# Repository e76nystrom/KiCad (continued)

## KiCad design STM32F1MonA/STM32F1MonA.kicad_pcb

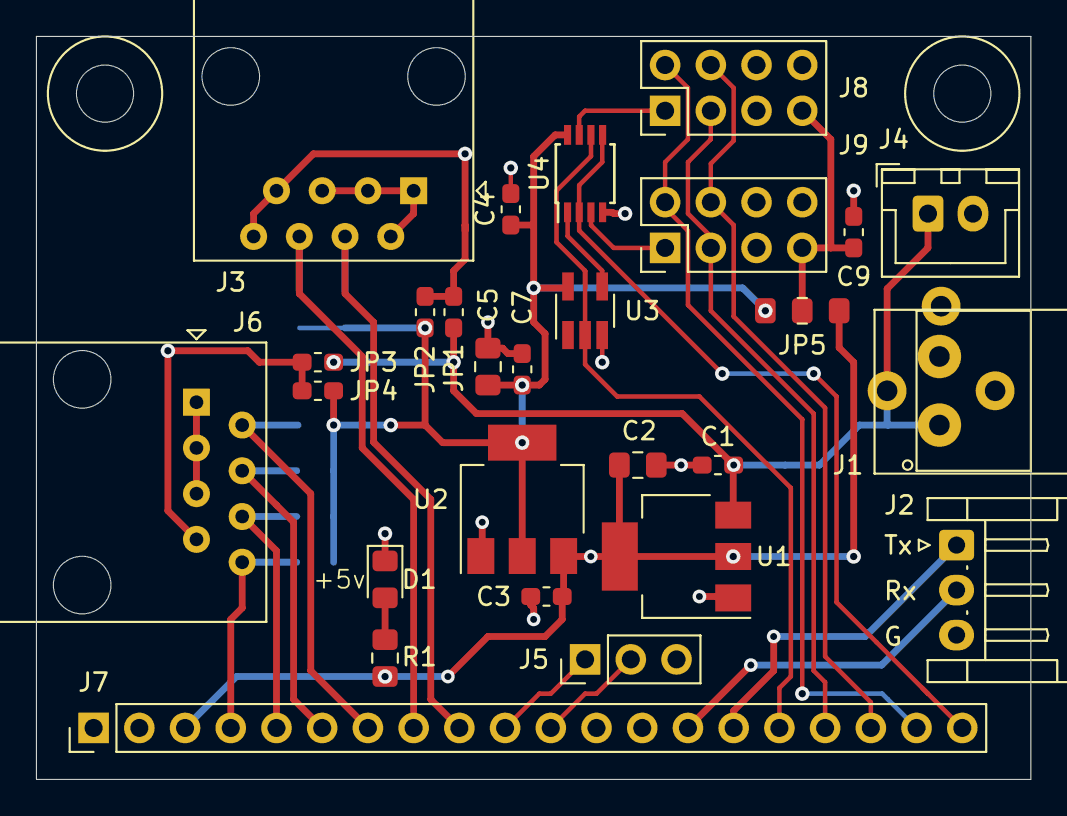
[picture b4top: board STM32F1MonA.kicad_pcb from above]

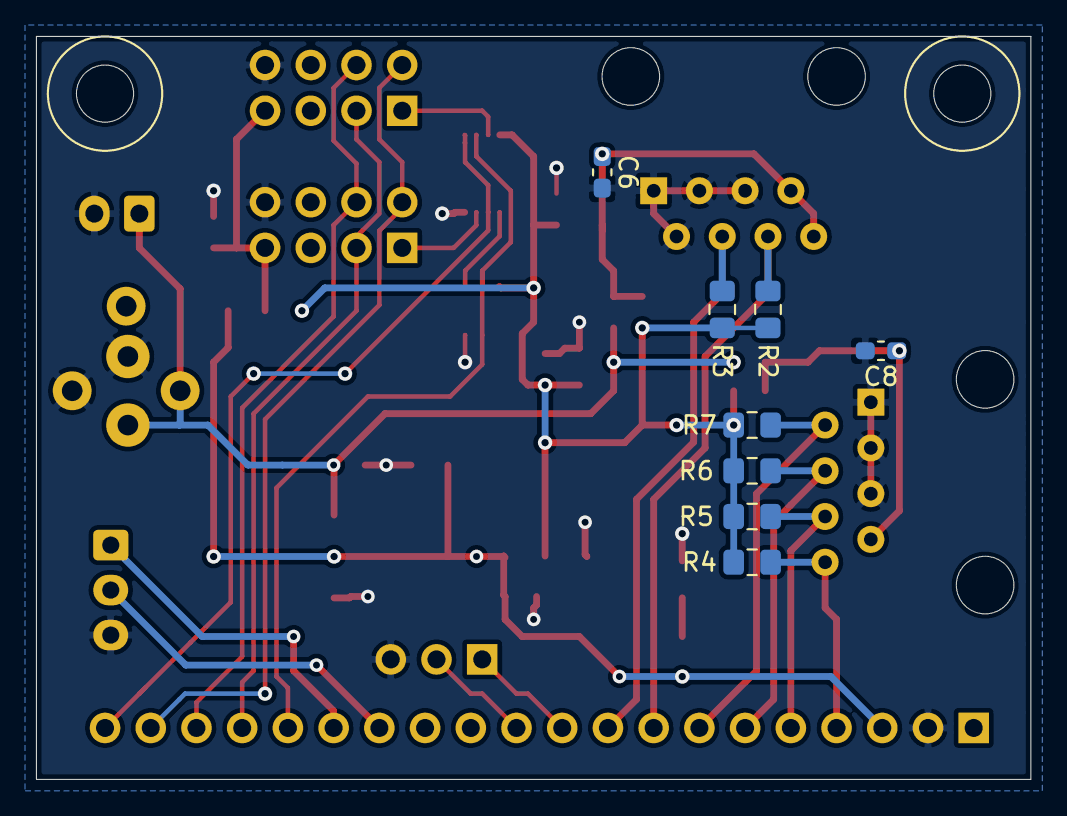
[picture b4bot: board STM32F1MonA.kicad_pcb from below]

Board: 2 copper layers, 55.2 x 41.3 mm, 37 parts (8 on the bottom side), 26 nets.

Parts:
C1, C3, C4, C6, C7, C8, C9: .1uf; C_0603_1608Metric_Pad1.05x0.95mm_HandSolder
C2, C5: 10u; C_0805_2012Metric_Pad1.15x1.40mm_HandSolder
D1: LED; D_0805_2012Metric_Pad1.15x1.40mm_HandSolder
H1, H2: MountingHole; MountingHole _1-8_1-4
J1: PJ-102; PJ-102-3.81mm
J2: Conn_01x03_Female; JST_EH_S3B-EH_1x03_P2.50mm_Horizontal
J3, J6: RJ45; RJ45_Amphenol_54602-x08_Horizontal
J4: Conn_01x02; JST_XH_B2B-XH-A_1x02_P2.50mm_Vertical
J5: Conn_01x03_Male; PinHeader_1x03_P2.54mm_Vertical
J7: Conn_01x20_Male; PinHeader_1x20_P2.54mm_Vertical
J8, J9: Conn_02x04_Odd_Even; PinHeader_2x04_P2.54mm_Vertical
JP1, JP2, JP3, JP4: Jumper_NO_Small; R_0603_1608Metric_Pad1.05x0.95mm_HandSolder
JP5: SolderJumper_3_Open; Jumper_0805_3
R1: 5.1k; R_0805_2012Metric_Pad1.15x1.40mm_HandSolder
R2, R3, R4, R5, R6, R7: R; R_0805_2012Metric_Pad1.15x1.40mm_HandSolder
U1: AP1117-50; SOT-223-3_TabPin2
U2: AP1117-33; SOT-223-3_TabPin2
U3: 74LVC1G04; SOT-23-5_HandSoldering
U4: 74LVC2G32; TSSOP-8_3x3mm_P0.65mm

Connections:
+3V3: C4.1, C5.1, C7.1, JP2.1, JP4.1, JP5.3, R2.1, R3.1, R4.1, R5.1, R6.1, R7.1, U2.2, U3.5, U4.8
+5V: C2.1, C3.1, J7.3, JP5.1, R1.1, U1.2, U2.3
/A8: J7.16, U3.2, U4.6
/A9: J2.1, J7.15
/A10: J2.2, J7.14
/A15: J5.2, J7.11
/B3: J5.1, J7.10
/B4: J3.4, J7.9, R3.2
/B5: J3.6, J7.8, R2.2
/B6: J6.2, J7.7, R7.2
/B7: J6.4, J7.6, R6.2
/B8: J6.6, J7.5, R5.2
/B9: J6.8, J7.4, R4.2
/B12: J7.20, U4.2, U4.5
/B13: J7.19, J8.2, J9.2
/B14: J7.18, J8.4, J9.4
/B15: J7.17, J8.3, J9.3
/LedR: D1.2, R1.2
/SensorPwr0: C6.1, J3.7, J3.8, JP1.2, JP2.2
/SensorPwr1: C8.1, J6.7, JP3.2, JP4.2
/VOut: C9.1, J8.7, J9.7, JP5.2
/Vin: C1.1, J1.1, J4.1, JP1.1, JP3.1, U1.3
/~CS0: J8.1, U4.7
/~CS1: J9.1, U4.3
/~Sel: U3.4, U4.1
GND: C1.2, C2.2, C3.2, C4.2, C5.2, C6.2, C7.2, C8.2, C9.2, D1.1, J1.2, J2.3, J3.1, J3.2, J3.3, J3.5, J4.2, J5.3, J6.1, J6.3, J6.5, J7.2, J8.8, J9.8, U1.1, U2.1, U3.3, U4.4

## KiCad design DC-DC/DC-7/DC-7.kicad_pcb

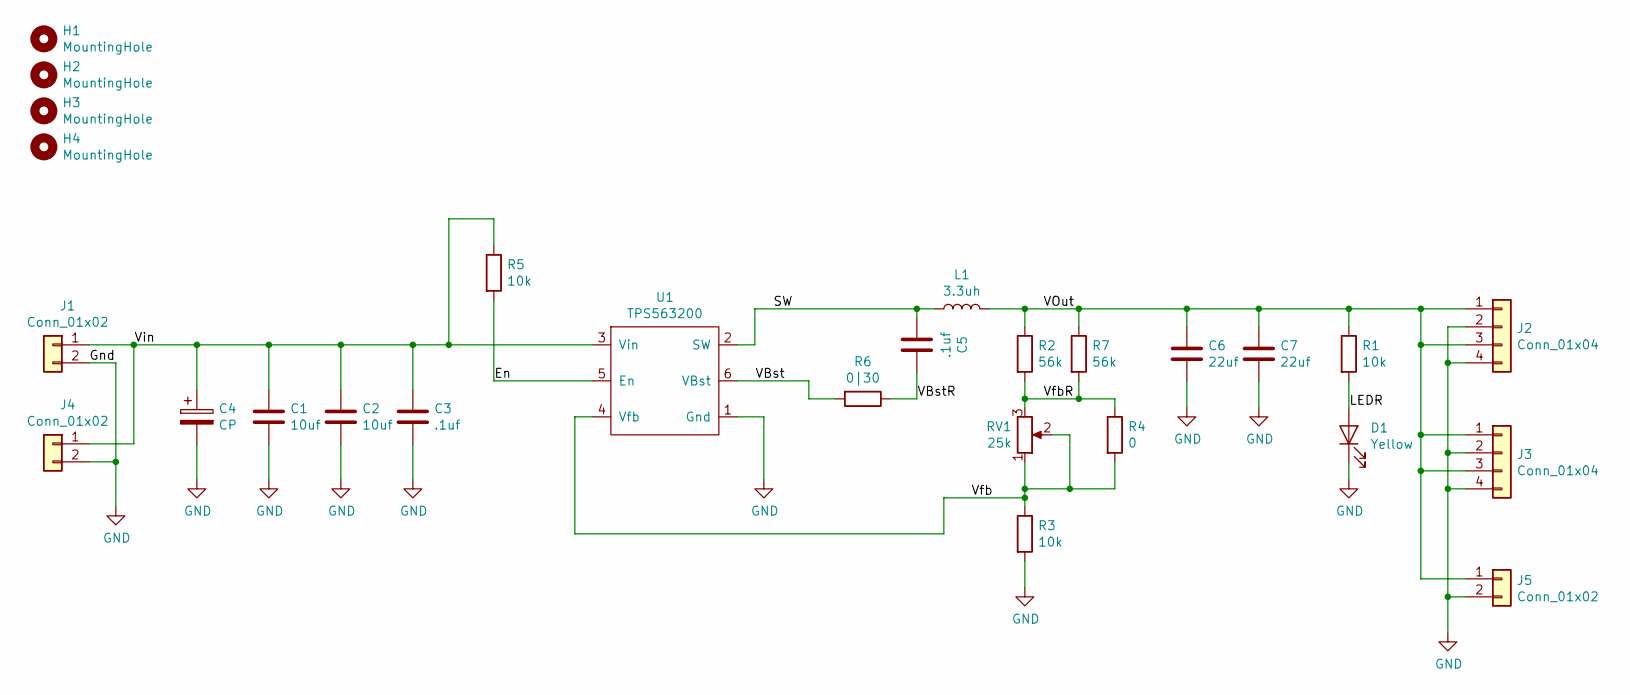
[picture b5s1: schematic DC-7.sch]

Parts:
C1, C2: 10uf; C_0603_1608Metric_Pad1.05x0.95mm_HandSolder
C3, C5: .1uf; C_0805_2012Metric_Pad1.15x1.40mm_HandSolder
C4: CP; CP_Radial_D10.0mm_P5.00mm
C6, C7: 22uf; C_1210_3225Metric_Pad1.42x2.65mm_HandSolder
D1: Yellow; LED_0805_2012Metric_Pad1.15x1.40mm_HandSolder
H1, H2, H3, H4: MountingHole; MountingHole _1-8_1-4
J1: Conn_01x02; 2 Pin 3.81mm
J2, J3: Conn_01x04; 4 Pin 3.81mm
J4, J5: Conn_01x02; PinHeader_1x02_P2.54mm_Vertical
L1: 3.3uh; KMP4800S
R1, R5: 10k; R_0805_2012Metric_Pad1.15x1.40mm_HandSolder
R2, R7: 56k; R_0805_2012Metric_Pad1.15x1.40mm_HandSolder
R3: 10k; R_0603_1608Metric_Pad1.05x0.95mm_HandSolder
R4: 0; R_0603_1608Metric_Pad1.05x0.95mm_HandSolder
R6: 0|30; R_0805_2012Metric_Pad1.15x1.40mm_HandSolder
RV1: 25k; Potentiometer_Bourns_3296W_Vertical
U1: TPS563200; SOT-23-6_Handsoldering

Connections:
/En: R5.2, U1.5 (En)
/LEDR: D1.2 (A), R1.2
/SW: C5.2, L1.1, U1.2 (SW)
/VBst: R6.2, U1.6 (VBst)
/VBstR: C5.1, R6.1
/VOut: C6.1, C7.1, J2.1, J2.3, J3.1, J3.3, J5.1, L1.2, R1.1, R2.1, R7.1
/Vfb: R3.1, R4.2, RV1.1, RV1.2, U1.4 (Vfb)
/VfbR: R2.2, R4.1, R7.2, RV1.3
/Vin: C1.1, C2.1, C3.1, C4.1, J1.1, J4.1, R5.1, U1.3 (Vin)
GND: C1.2, C2.2, C3.2, C4.2, C6.2, C7.2, D1.1 (K), J1.2, J2.2, J2.4, J3.2, J3.4, J4.2, J5.2, R3.2, U1.1 (Gnd)

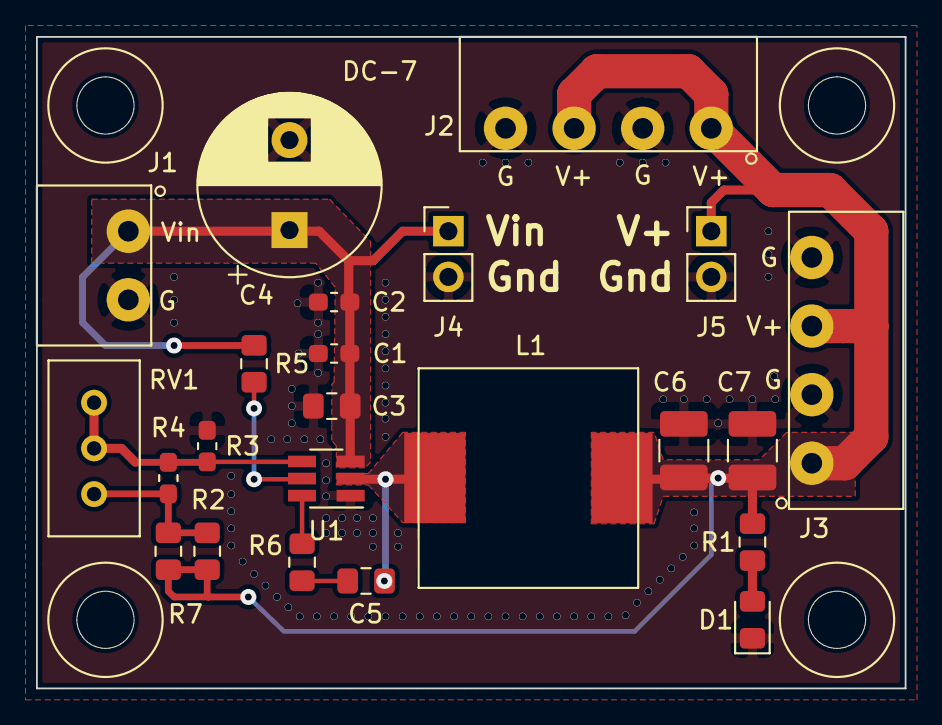
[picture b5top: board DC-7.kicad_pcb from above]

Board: 2 copper layers, 48.3 x 36.2 mm, 27 parts (0 on the bottom side), 10 nets.

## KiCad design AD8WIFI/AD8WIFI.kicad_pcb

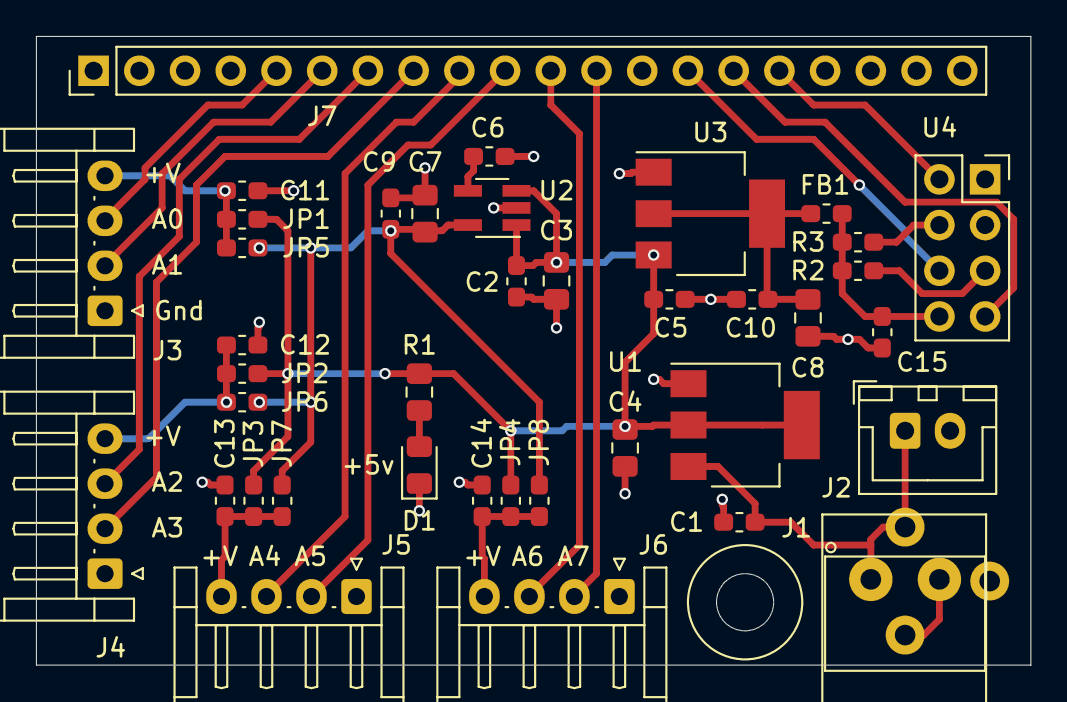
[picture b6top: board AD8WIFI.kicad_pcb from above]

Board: 2 copper layers, 55.2 x 34.9 mm, 40 parts (0 on the bottom side), 25 nets.

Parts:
C1, C2, C5, C9, C10, C11, C12, C13, C14, C15: .1uf; C_0603_1608Metric_Pad1.05x0.95mm_HandSolder
C3, C4, C7, C8: 10u; C_0805_2012Metric_Pad1.15x1.40mm_HandSolder
C6: .1u; C_0603_1608Metric_Pad1.05x0.95mm_HandSolder
D1: LED; D_0805_2012Metric_Pad1.15x1.40mm_HandSolder
FB1: Ferrite_Bead; L_0603_1608Metric_Pad1.05x0.95mm_HandSolder
H1: MountingHole; MountingHole _1-8_1-4
J1: PJ-102; PJ-102-3.81mm
J2: Conn_01x02; JST_XH_B2B-XH-A_1x02_P2.50mm_Vertical
J3, J4, J5, J6: Conn_01x04_Female; JST_EH_S4B-EH_1x04_P2.50mm_Horizontal
J7: Conn_01x20_Male; PinHeader_1x20_P2.54mm_Vertical
JP1, JP2, JP3, JP4, JP5, JP6, JP7, JP8: Jumper_NO_Small; R_0603_1608Metric_Pad1.05x0.95mm_HandSolder
R1: 5.1k; R_0805_2012Metric_Pad1.15x1.40mm_HandSolder
R2, R3: 10k; R_0603_1608Metric_Pad1.05x0.95mm_HandSolder
U1: AP1117-50; SOT-223-3_TabPin2
U2: RT9193; SOT-23-5_HandSoldering
U3: AP1117-33; SOT-223-3_TabPin2
U4: ESP8266; ESP-01

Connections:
+3V3: C7.1, C9.1, JP5.1, JP6.1, JP7.1, JP8.1, U2.5
+5V: C2.1, C3.1, C4.1, C5.1, JP1.1, JP2.1, JP3.1, JP4.1, R1.1, U1.2, U2.1, U2.3, U3.3
/3.3W: C8.1, C10.1, FB1.1, U3.2
/A0: J3.3, J7.5
/A1: J3.2, J7.6
/A2: J4.3, J7.7
/A3: J4.2, J7.8
/A4: J5.3, J7.9
/A5: J5.2, J7.10
/A6: J6.3, J7.11
/A7: J6.2, J7.12
/B1-Rst: J7.14, U4.6
/B10-Tx: J7.15, U4.7
/B11-Rx: J7.16, U4.2
/BP: C6.1, U2.4
/ESP3.3: C15.1, FB1.2, R2.1, R3.1, U4.8
/LedR: D1.2, R1.2
/Pu0: R2.2, U4.5
/Pu1: R3.2, U4.4
/VA0: C11.2, J3.4, JP1.2, JP5.2
/VA1: C12.2, J4.4, JP2.2, JP6.2
/VA2: C13.2, J5.4, JP3.2, JP7.2
/VA3: C14.2, J6.4, JP4.2, JP8.2
/Vin: C1.1, J1.1, J2.1, U1.3
GND: C1.2, C2.2, C3.2, C4.2, C5.2, C6.2, C7.2, C8.2, C9.2, C10.2, C11.1, C12.1, C13.1, C14.1, C15.2, D1.1, J1.2, J2.2, J3.1, J4.1, J5.1, J6.1, J7.19, J7.20, U1.1, U2.2, U3.1, U4.1

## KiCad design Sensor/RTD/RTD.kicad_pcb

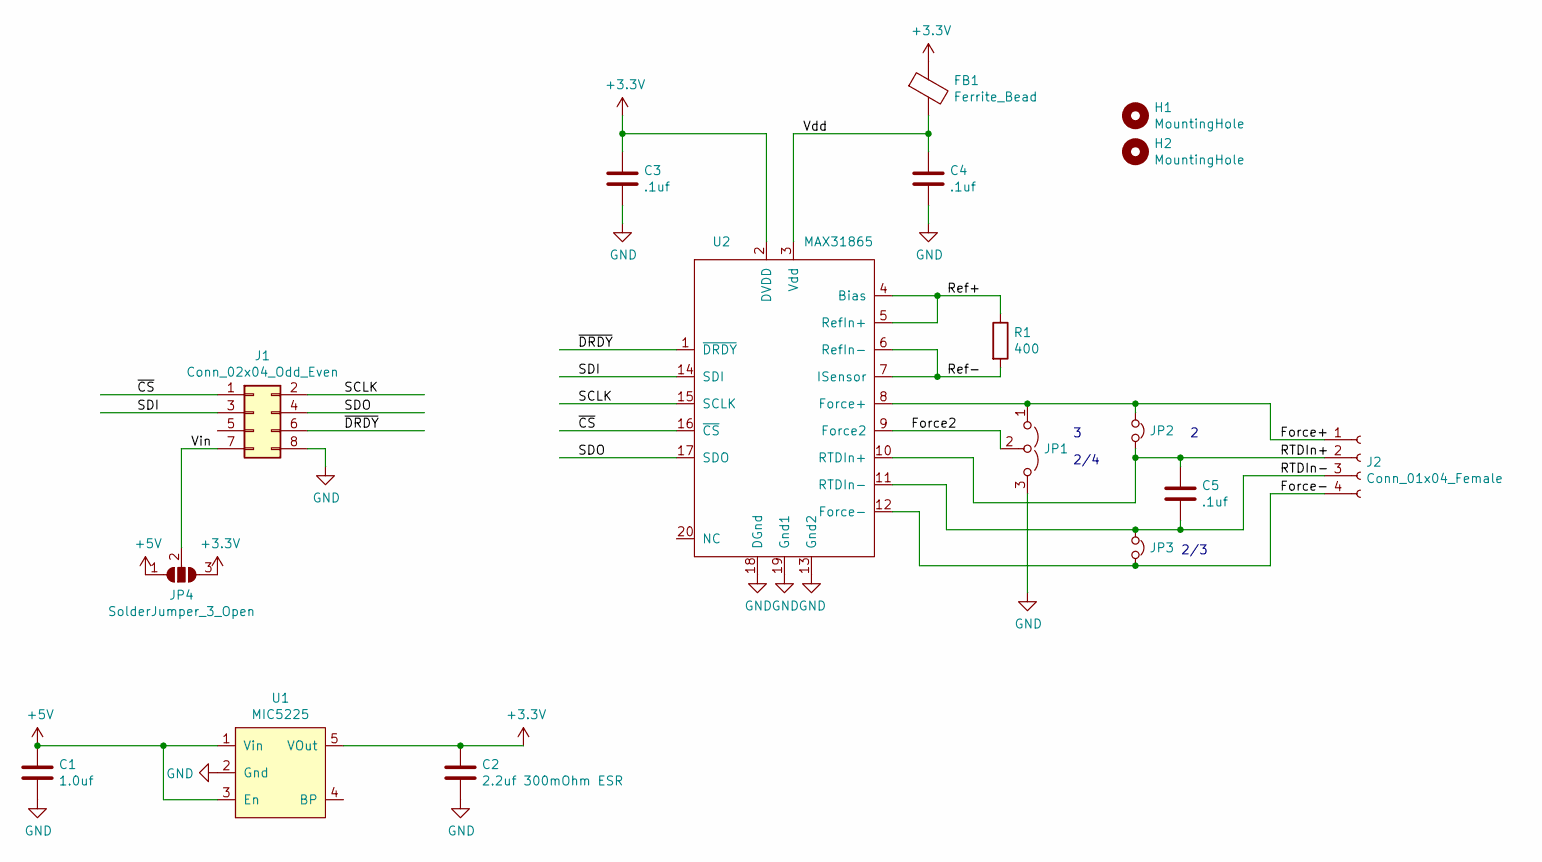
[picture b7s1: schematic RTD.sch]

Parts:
C1: 1.0uf; C_0805_2012Metric_Pad1.15x1.40mm_HandSolder
C2: 2.2uf 300mOhm ESR; C_0805_2012Metric_Pad1.15x1.40mm_HandSolder
C3, C4, C5: .1uf; C_0805_2012Metric_Pad1.15x1.40mm_HandSolder
FB1: Ferrite_Bead; L_0805_2012Metric_Pad1.15x1.40mm_HandSolder
H1, H2: MountingHole; MountingHole _1-8_1-4
J1: Conn_02x04_Odd_Even; PinHeader_2x04_P2.54mm_Vertical
J2: Conn_01x04_Female; PhoenixContact_MC_1,5_4-G-3.81_1x04_P3.81mm_Horizontal
JP1: SolderJumper-3_P1.3mm_Open_RoundedPad1.0x1.5mm_NumberLabels
JP2, JP3: SolderJumper-2_P1.3mm_Open_TrianglePad1.0x1.5mm
JP4: SolderJumper_3_Open; Jumper_0805_3
R1: 400; R_0805_2012Metric_Pad1.15x1.40mm_HandSolder
U1: MIC5225; SOT-23-5_HandSoldering
U2: MAX31865; TSSOP-20_4.4x6.5mm_P0.65mm_MAX

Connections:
+3V3: C2.1, C3.1, FB1.1, JP4.3 (B), U1.5 (VOut), U2.2 (DVDD)
+5V: C1.1, JP4.1 (A), U1.1 (Vin), U1.3 (En)
/Force2: JP1.2 (C), U2.9 (Force2)
/Force+: J2.1, JP1.1 (A), JP2.1, U2.8 (Force+)
/Force-: J2.4, JP3.2, U2.12 (Force-)
/RTDIn+: C5.1, J2.2, JP2.2, U2.10 (RTDIn+)
/RTDIn-: C5.2, J2.3, JP3.1, U2.11 (RTDIn-)
/Ref+: R1.1, U2.4 (Bias), U2.5 (RefIn+)
/Ref-: R1.2, U2.6 (RefIn-), U2.7 (ISensor)
/SCLK: J1.2, U2.15 (SCLK)
/SDI: J1.3, U2.14 (SDI)
/SDO: J1.4, U2.17 (SDO)
/Vdd: C4.2, FB1.2, U2.3 (Vdd)
/Vin: J1.7, JP4.2 (C)
/~CS: J1.1, U2.16 (~CS)
/~DRDY: J1.6, U2.1 (~DRDY)
GND: C1.2, C2.2, C3.2, C4.1, J1.8, JP1.3 (B), U1.2 (Gnd), U2.13 (Gnd2), U2.18 (DGnd), U2.19 (Gnd1)

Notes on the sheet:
2/4
2/3

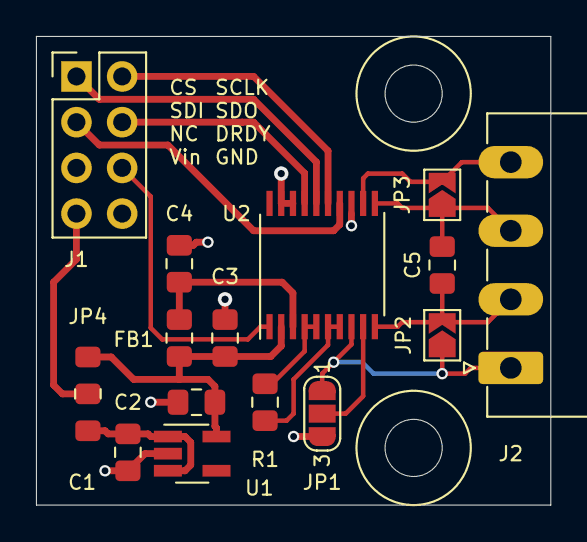
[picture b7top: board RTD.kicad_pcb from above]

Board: 2 copper layers, 28.6 x 26.0 mm, 17 parts (0 on the bottom side), 17 nets.

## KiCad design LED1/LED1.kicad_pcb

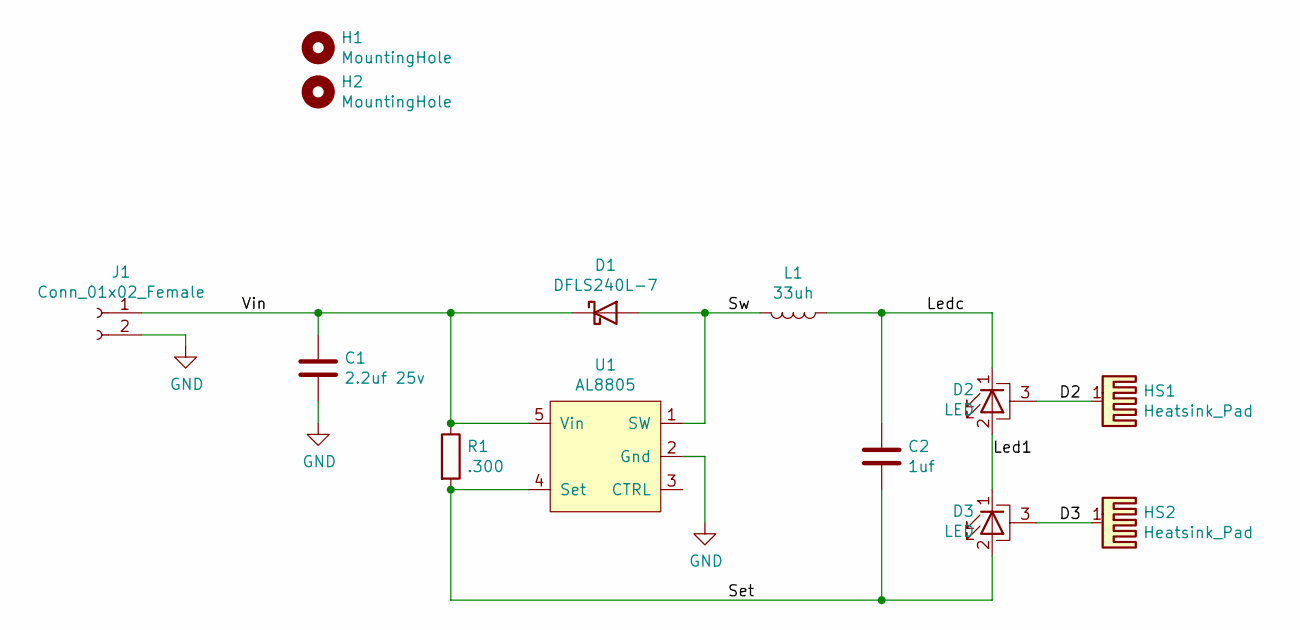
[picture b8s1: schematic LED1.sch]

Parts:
C1: 2.2uf 25v; C_0805_2012Metric_Pad1.15x1.40mm_HandSolder
C2: 1uf; C_1206_3216Metric_Pad1.42x1.75mm_HandSolder
D1: DFLS240L-7; D_SOD-123
D2, D3: LED; PowerLed
H1, H2: MountingHole; MountingHole _1-8_1-4
HS1, HS2: Heatsink_Pad
J1: Conn_01x02_Female; PhoenixContact_MC_1,5_2-G-3.81_1x02_P3.81mm_Horizontal
L1: 33uh; LPS-6235
R1: .300; R_0805_2012Metric_Pad1.15x1.40mm_HandSolder
U1: AL8805; SOT-23-5_HandSoldering

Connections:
/D2: D2.3 (PAD), HS1.1
/D3: D3.3 (PAD), HS2.1
/Led1: D2.2 (A), D3.1 (K)
/Ledc: C2.1, D2.1 (K), L1.1
/Set: C2.2, D3.2 (A), R1.2, U1.4 (Set)
/Sw: D1.2 (A), L1.2, U1.1 (SW)
/Vin: C1.1, D1.1 (K), J1.1, R1.1, U1.5 (Vin)
GND: C1.2, J1.2, U1.2 (Gnd)

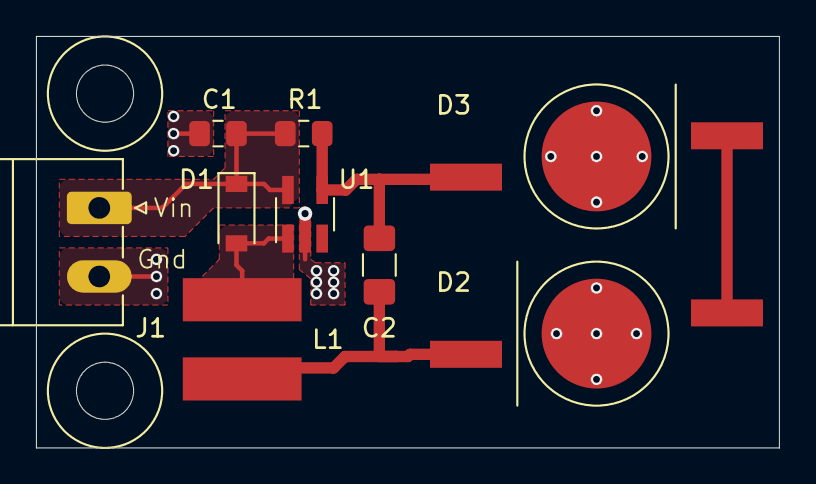
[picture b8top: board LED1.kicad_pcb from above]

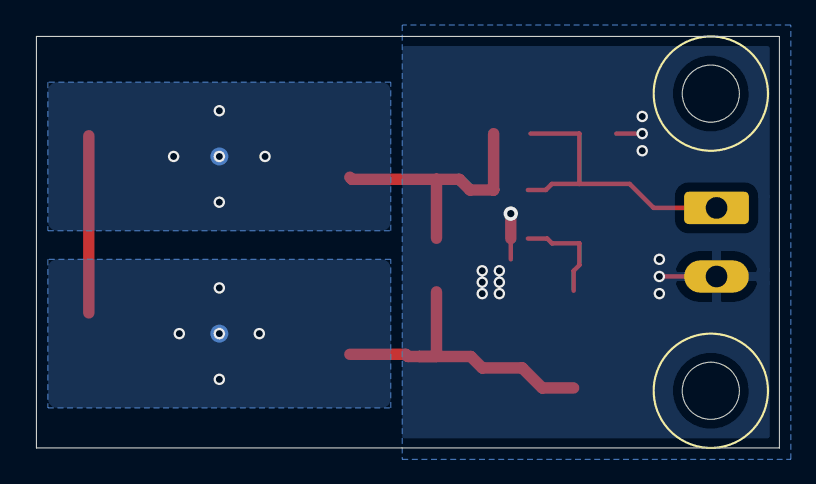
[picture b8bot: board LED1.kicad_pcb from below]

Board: 2 copper layers, 41.3 x 22.9 mm, 13 parts (2 on the bottom side), 8 nets.

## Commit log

2021-01-01 New layout for Mega Output. Part done
2021-01-01 Output Mega layout completed.
2021-01-01 Add labels to silk screen.
2021-01-03 Designed front panel. More updates to output.
2021-01-03 Add ferrite and capacitor to filter VFD control voltage.
2021-01-12 Boards sent to be built.
2021-01-21 FT4232 Board and some fixes/
2021-01-28 Updates for new boards.
2021-02-08 Update LED resistor values.
2021-02-12 Fix footprint. Fix wiring for connector.
2021-02-18 Updating component values. Updates for new Kicad version.
2021-02-25 Update values on PCB.
2021-02-26 STM32F1 board with different crystals.
2021-03-03 Updates while making boards.
2021-03-18 Updates to component values.
2021-03-18 Update spreadsheets.
2021-03-23 Add USB hub.
2021-03-23 Update to USB hub.
2021-03-24 STM32F1 new layout.
